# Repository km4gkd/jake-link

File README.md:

# usb-link
a cheap sound card interface for amature radio inculding vox 
note there is no led in the circuit board
also note 2n2222 transistors are used insted of 2N3904 but eithe can be used
i desided to change the name to jake-link

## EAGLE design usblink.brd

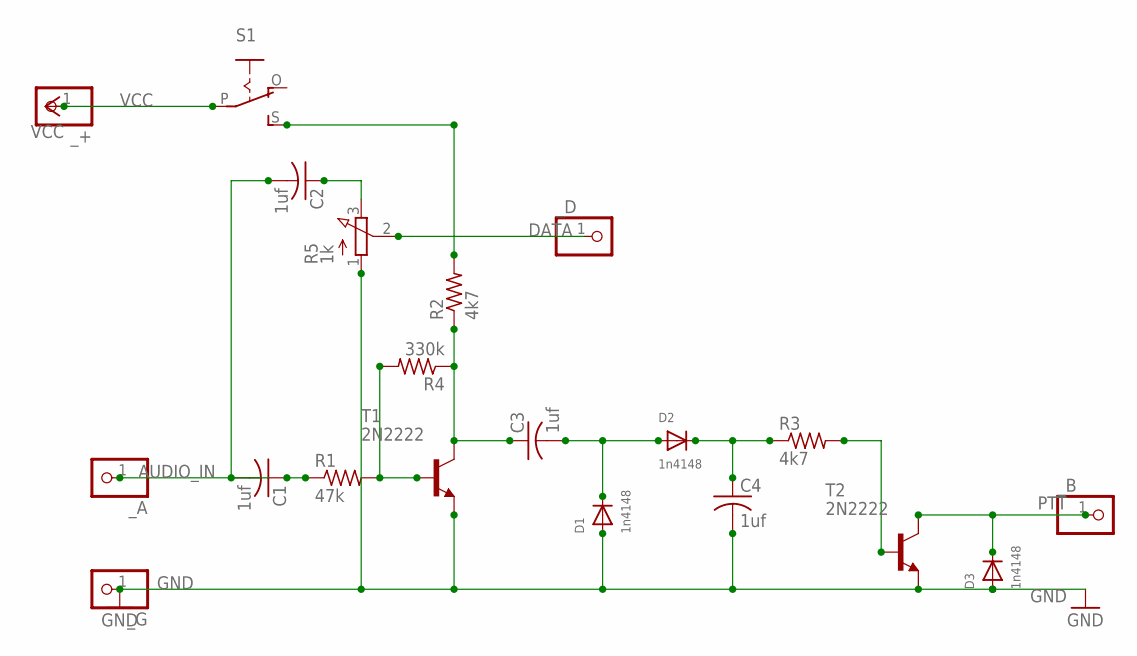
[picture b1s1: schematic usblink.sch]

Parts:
C1, C2, C3, C4: 1uf; C025-030X050
D1, D2, D3: 1n4148; DO-1N4148
R1: 47k; 0204/7
R2, R3: 4k7; 0204/7
R4: 330k; 0204/7
R5: 1k; 3RP/1610N
S1: EG1218S; EG1218
T1, T2: 2N2222; TO92-EBC-OVAL
_+: PINHD-1X1CB; 1X01-CLEANBIG
_A: PINHD-1X1CB; 1X01-CLEANBIG
_B: PINHD-1X1CB; 1X01-CLEANBIG
_D: PINHD-1X1CB; 1X01-CLEANBIG
_G: PINHD-1X1CB; 1X01-CLEANBIG

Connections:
AUDIO_IN: C1.2, C2.2, _A.1
DATA: R5.2 (S), _D.1
GND: C4.2, D1.A, D3.A, R5.1 (A), T1.E, T2.E, _G.1
unnamed: R2.2, S1.S
unnamed: C2.1, R5.3 (E)
unnamed: C1.1, R1.1
unnamed: R1.2, R4.2, T1.B
unnamed: C3.1, R2.1, R4.1, T1.C
unnamed: C3.2, D1.C, D2.A
unnamed: C4.1, D2.C, R3.1
unnamed: R3.2, T2.B
PTT: D3.C, T2.C, _B.1
VCC: S1.P, _+.1

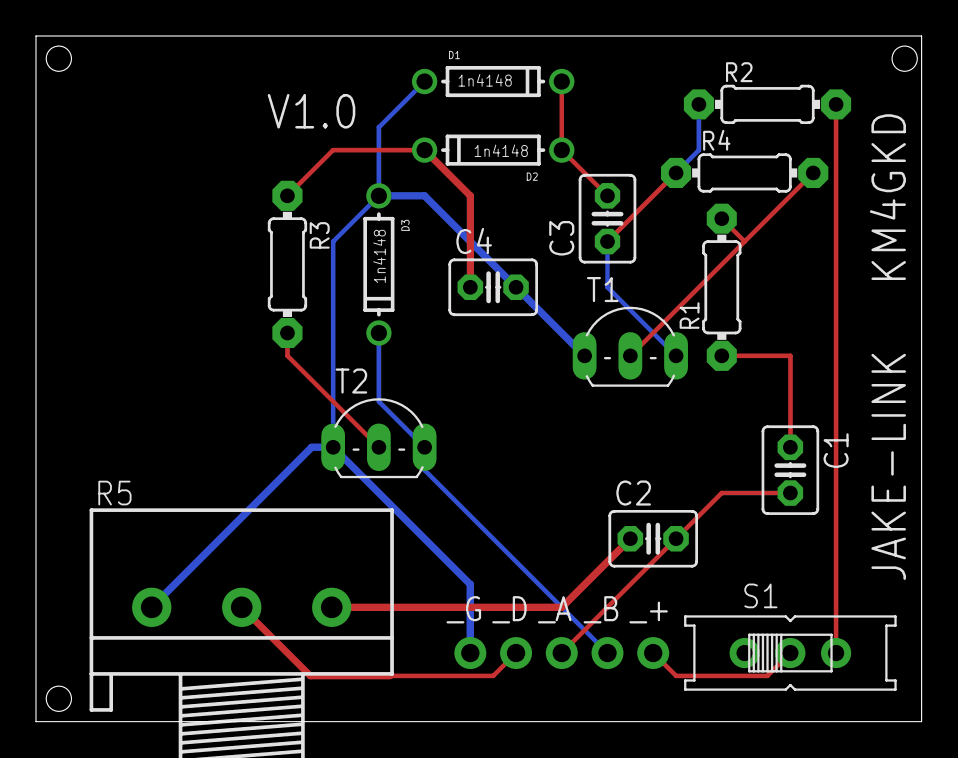
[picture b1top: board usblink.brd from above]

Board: 2 copper layers, 49.2 x 38.1 mm, 20 parts (0 on the bottom side), 13 nets.
